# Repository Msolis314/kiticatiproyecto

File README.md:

# kiticatiproyecto
Monometer exacto,preciso y estable

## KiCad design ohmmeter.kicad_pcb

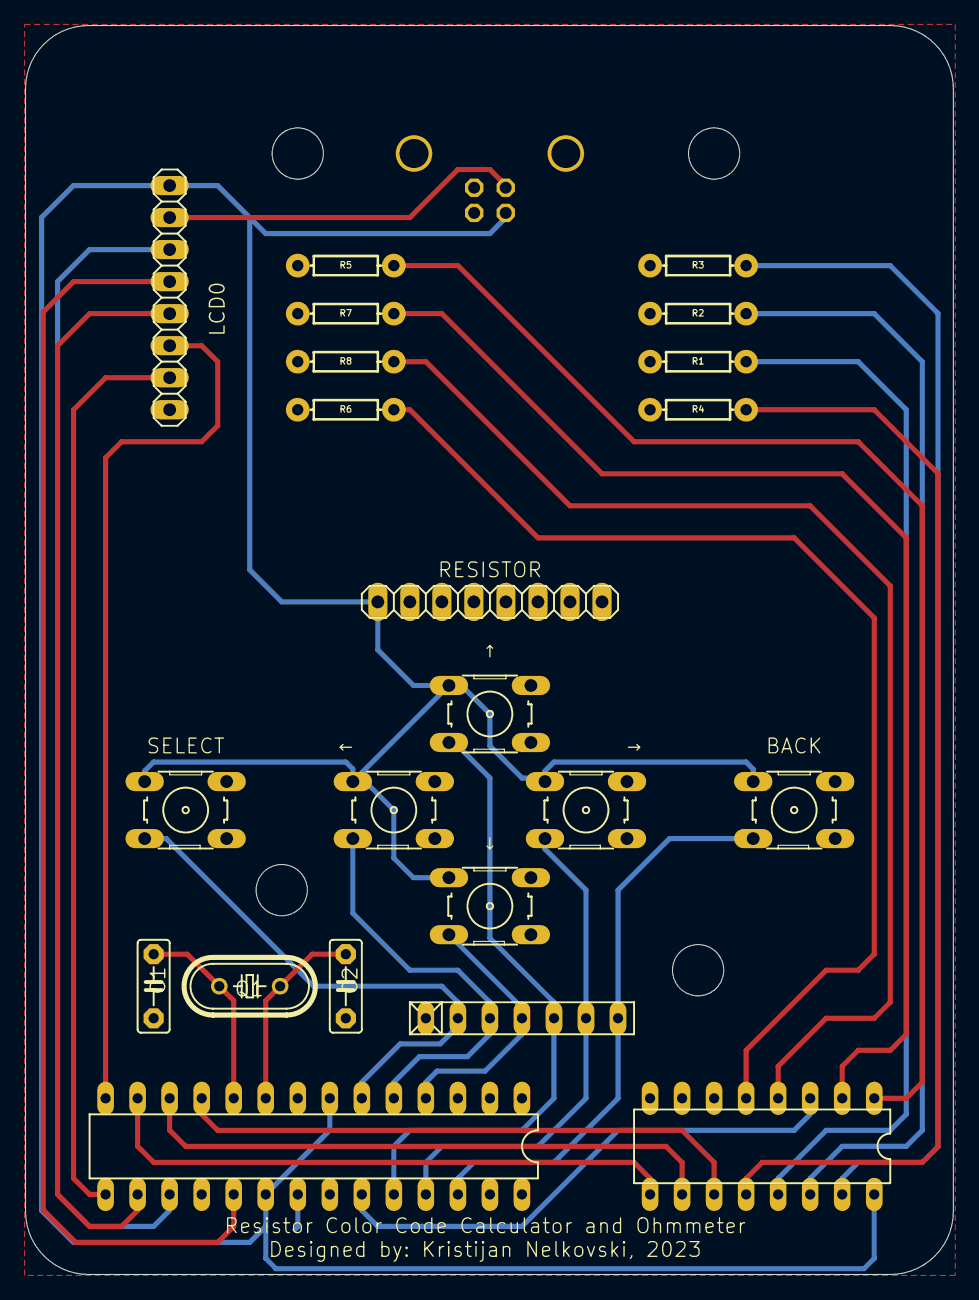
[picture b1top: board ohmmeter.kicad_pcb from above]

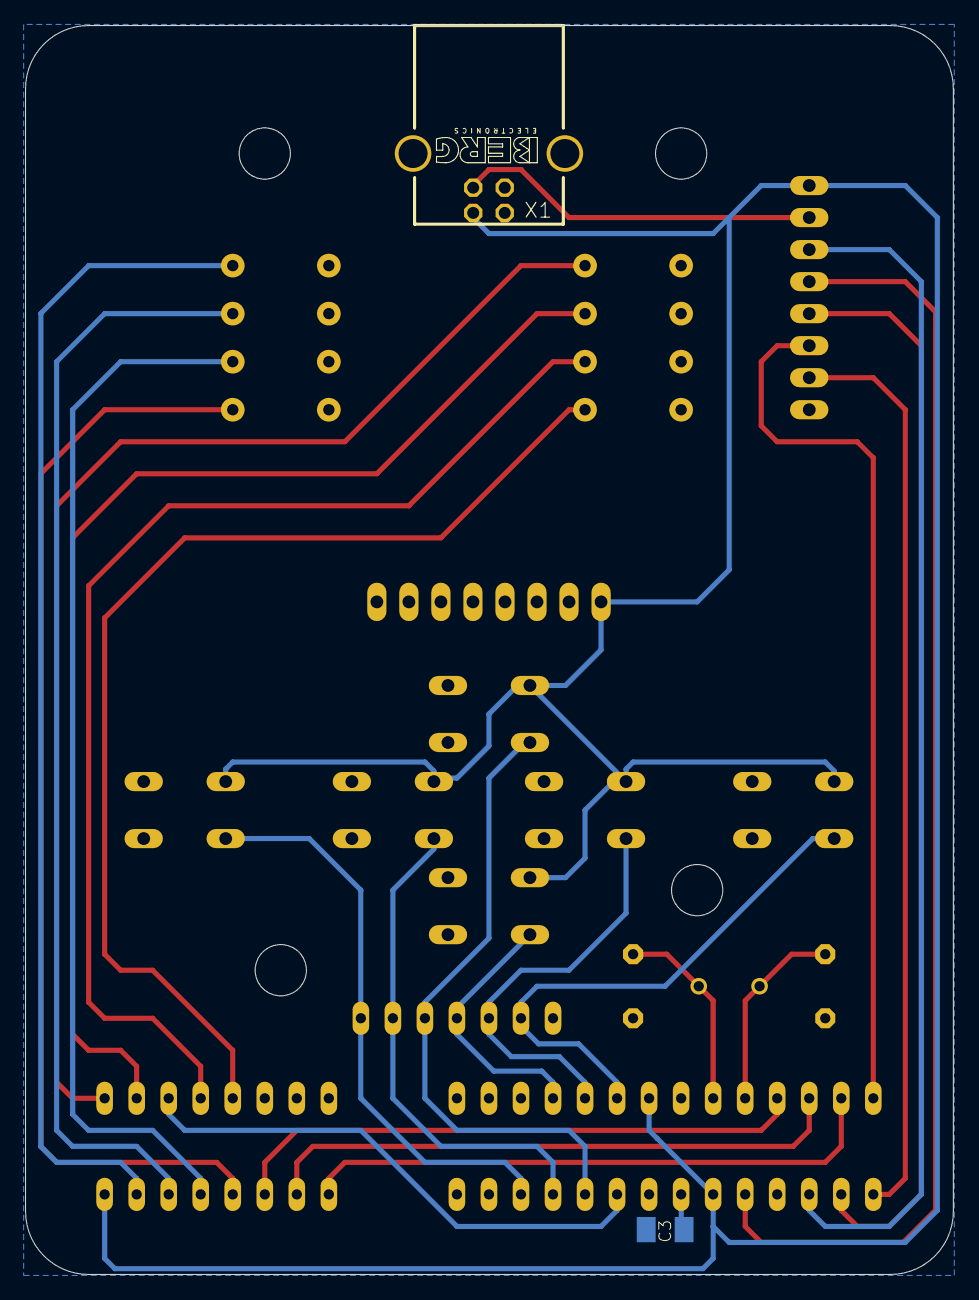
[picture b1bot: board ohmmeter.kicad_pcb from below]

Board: 2 copper layers, 73.6 x 99.1 mm, 28 parts (2 on the bottom side), 28 nets.

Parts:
@HOLE0, @HOLE1, @HOLE2, @HOLE3: (no value)
BUTTON1, BUTTON2, BUTTON3, BUTTON4, BUTTON5, BUTTON6: B3F-10XX_377
C1, C2: C5B2.5_116
C3: C1206K_334
IC1: ATMEGA328-20P; DIL28-3
IC2: 4051N; DIL16_80
LCD0: 1X08_325
Q1: HC49U-V_204
R1, R2, R3, R4, R5, R6, R7, R8: AXIAL-0.3
RESISTOR_NET0: RN-7_343
RESISTOR_PORT0: 1X08_325
X1: PN61729-S; PN61729-S_130

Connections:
A: IC1.11, IC2.11
B: IC1.12, IC2.10
B1: BUTTON1.3, IC1.6, RESISTOR_NET0.2
B2: BUTTON2.3, IC1.5, RESISTOR_NET0.3
B3: BUTTON3.3, IC1.4, RESISTOR_NET0.4
B4: BUTTON4.3, IC1.24, RESISTOR_NET0.5
B5: BUTTON5.3, IC1.25, RESISTOR_NET0.6
B6: BUTTON6.3, IC1.26, RESISTOR_NET0.7
C: IC1.13, IC2.9
CLK: IC1.19, LCD0.4
CS: IC1.16, LCD0.5
DC: IC1.14, LCD0.6
DIN: IC1.17, LCD0.3
GND: C1.1, C2.1, C3.1, IC1.8, IC1.22, IC2.6, IC2.8, LCD0.2, R1.P$1, R2.P$1, R3.P$1, R4.P$1, R5.P$1, R6.P$1, R7.P$1, R8.P$1, RESISTOR_NET0.1, X1.4
INPUT: IC2.3, RESISTOR_PORT0.1
unnamed: C2.2, IC1.9, Q1.2
unnamed: C1.2, IC1.10, Q1.1
unnamed: IC2.1, R5.P$2
unnamed: IC2.13, R1.P$2
unnamed: IC2.12, R4.P$2
unnamed: IC2.14, R2.P$2
unnamed: IC2.15, R3.P$2
unnamed: IC2.5, R6.P$2
unnamed: IC2.2, R7.P$2
unnamed: IC2.4, R8.P$2
unnamed: C3.2, IC1.21
RST: IC1.15, LCD0.7
VCC: BUTTON1.1, BUTTON2.1, BUTTON3.1, BUTTON4.1, BUTTON5.1, BUTTON6.1, IC1.7, IC1.20, IC2.16, LCD0.1, RESISTOR_PORT0.8, X1.1

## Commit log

2024-11-13 Primer Commit con el proyecto del amiguito del internet
